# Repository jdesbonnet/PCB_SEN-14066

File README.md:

# Projects related to Sparkfun SEN-14066 UHF RFID board

## SEN-14066-adapter

Buffer SEN-14066 TXO / UART RX with two 7404 NOT gates. Optional buffering of the RXI / UART TX also. 
See [SEN-14066 troubleshooting](https://github.com/jdesbonnet/SEN-14066_Troubleshooting) for 
some background information.

Sent to OSHPark for fabrication on 2018-07-15.

https://oshpark.com/shared_projects/R4Yin0K0

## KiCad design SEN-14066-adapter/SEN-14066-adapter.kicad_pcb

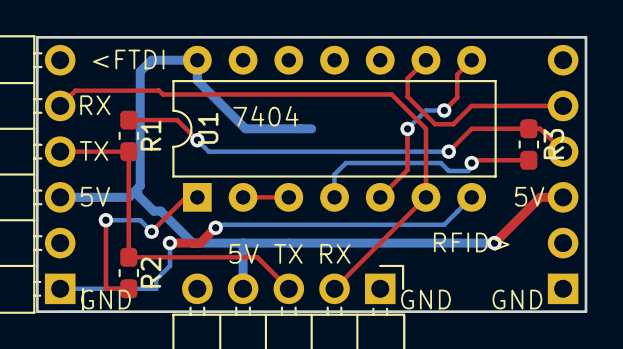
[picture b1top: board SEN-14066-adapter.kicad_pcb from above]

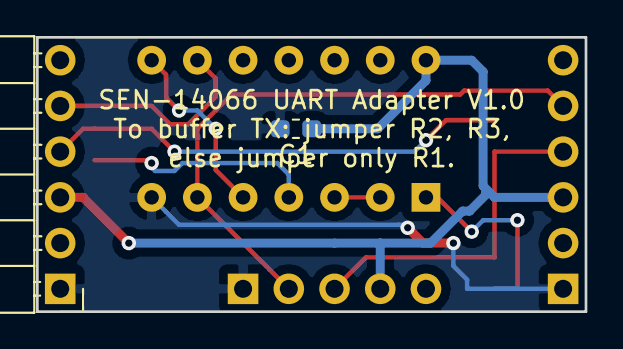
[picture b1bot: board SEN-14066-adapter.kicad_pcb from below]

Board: 2 copper layers, 30.5 x 15.2 mm, 8 parts (2 on the bottom side), 10 nets.

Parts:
C1: 500n; C_0603_1608Metric_Pad1.05x0.95mm_HandSolder
J1: Conn_01x06_Male; PinHeader_1x06_P2.54mm_Horizontal
J2: Conn_01x05_Female; PinHeader_1x05_P2.54mm_Horizontal
J3: Conn_01x06_Female; PinHeader_1x06_P2.54mm_Horizontal
R1, R2, R3: R; R_0603_1608Metric_Pad1.05x0.95mm_HandSolder
U1: 74HC04; DIP-14_W7.62mm

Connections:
GND: C1.2, J1.1, J2.1, J3.1, U1.7
unnamed: J3.4, R1.2, R3.1
unnamed: J3.5, U1.9
unnamed: R2.1, U1.1
unnamed: R3.2, U1.4
unnamed: U1.2, U1.3
unnamed: U1.5, U1.8
RXD: J1.5, J2.2, U1.6
TXD: J1.4, J2.3, R1.1, R2.2
Vcc: C1.1, J1.3, J2.4, J3.3, U1.14

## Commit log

2018-07-15 no comment
2018-07-15 gerber and drill files
2018-07-15 PCB images
2018-08-18 schematic
